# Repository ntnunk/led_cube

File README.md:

8x8x8 LED Cube
----

My 8x8x8 LED Cube project. This repository will eventually contain both code and circuit schematics.
Schematics and printed circuit boards designed in Kicad.

### Concept

The cube is composed of eight layers of eight LEDs per side, or sixty-four LEDs per layer. The cube
relies upon persistance of vision, much like a flourescent light, which means there is never
actually more than one LED layer active at a time. Because the controller cycles through the layers
so quickly it fools the human eye and appears as though the cube is lit continuously.

The LED cube itself is constructed of layers and columns of LEDs. The anodes every LED in a given
column are connected together while the cathodes of every LED in a given layer are connected
together. Individual LEDs can be turned on by having power applied to the vertical column the LED is
part of and then having the layer it's part of switched to ground.

## Functionality

#### Controller and Decoder

The controller for this project is essentially a simplified Arduino Duemilanove with an ATMEL
ATMEGA328P processor. A 74HC238 3-to-8 decoder is used to select one of eight general purpose NPN
transistors. The eight transistors have the base connected to an output pin of the decoder, the
emitter to ground, and the collector to the cathodes of the LEDs in the transistor's associated
layer. Since the cathodes of all LEDs on a given layer are connected together, turning on one of the
layer enable transistors connects the cathodes of that layer's LEDs to ground, causing any LEDs in
the layer with power applied to their anodes to turn on.

#### LED Driver

The second major section is the LED driver. Since the controller doesn't have enough GPIO pins to
control the number of LEDs required, another 74HC238 3-to-8 decoder is used in conjunction with
eight 74HC595N serial-in, parallel-out 8-bit shift registers to control the 64 LEDs on a layer. The
shift registers could be connected in serial, removing the need for the extra decoder, but that
would require 64 clock cycles per layer change to push all the LED enable bits into the 8
daisy-chained shift registers. Instead, the shift registers are connected in parallel with each
shift register IC (integrated circuit) controlling an individual LED on each row of the layer. So,
for example, the first 8-bit shift register controls the first LED in all eight of the rows on a
layer. 

#### Operation

The processor enables the three input lines on the decoder chip based on which LEDs on the first
row are indicated by the control program. The decoder sets the 8 output lines based on the 3 input
lines. The 8 output lines are sent to the serial in of each shift register, the processor toggles
the serial clock to move the shift registers one position, then the process repeats until all 8
output lines of all 8 shift registers are set as desired for the layer. 

The shift register output lines drive the anodes of all the LEDs on the layer. Once the processor
switches the cathodes of the layer to ground via the layer enable transistors as described above,
the enabled LEDs in the layer will light up and stay lit until the processor sets up and enables the
next layer in the sequence.

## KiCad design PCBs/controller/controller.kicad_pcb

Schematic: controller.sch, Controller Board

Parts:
C1, C9, C10: 0.1uF; CP_Radial_Tantal_D5.0mm_P2.50mm
C2: 1000uF; CP_Radial_D8.0mm_P3.50mm
C3, C7, C11: 10uF; CP_Radial_D5.0mm_P2.00mm
C4: 0.1uF; C_Disc_D8.0mm_W2.5mm_P5.00mm
C5, C6: 22pF; C_Disc_D4.7mm_W2.5mm_P5.00mm
C8: 0.1uF; CP_Radial_D5.0mm_P2.00mm
D1: LED; LED_D5.0mm
D2, D3: 1N4001; D_T-1_P5.08mm_Horizontal
J1: +12V_IN; PINHEAD1-2
J2: PWR_SW; PINHEAD1-2
J3: SERIAL; PINHEAD1-6
J4: PROG; IDC_Header_Straight_6pins
J5: +5V_OUT; PINHEAD1-2
J6: DRV_SIG1; IDC_Header_Straight_8pins
J7: DRV_SIG2; IDC_Header_Straight_8pins
J8: LAYER_EN; IDC_Header_Straight_8pins
Q1, Q2, Q3, Q4, Q5, Q6, Q7, Q8: 2N3700; TO-92_Molded_Narrow
R1, R4: 1K; R_Axial_DIN0207_L6.3mm_D2.5mm_P10.16mm_Horizontal
R2, R3: 10k; R_Axial_DIN0207_L6.3mm_D2.5mm_P10.16mm_Horizontal
R5, R6, R7, R8, R9, R10, R11, R12, R13: 330; R_Axial_DIN0207_L6.3mm_D2.5mm_P10.16mm_Horizontal
SW1: DBG_SW; SW_PUSH_6mm
SW2: RESET_SW; SW_PUSH_6mm
U1: ATMEGA328-PU; DIP-28_W7.62mm_Socket
U2: LM317T; TO-220
U3, U4: 74HC238; DIP-16_W7.62mm_Socket
Y1: 16MHz; Crystal_HC49-U_Vertical

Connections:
+5V: C1.1, C9.1, C10.1, R2.2, R3.2, U1.7 (VCC), U1.20 (AVCC), U3.16 (VCC), U4.16 (VCC)
/+12VDC: C2.1, C3.1, C4.1, D1.2 (A), D2.1 (K), J2.2, U2.1 (IN)
/B1_SER1: J6.1, U3.15 (Y0)
/B1_SER2: J6.2, U3.14 (Y1)
/B1_SER3: J6.3, U3.13 (Y2)
/B1_SER4: J6.4, U3.12 (Y3)
/B2_SER5: J7.1, U3.11 (Y4)
/B2_SER6: J7.2, U3.10 (Y5)
/B2_SER7: J7.3, U3.9 (Y6)
/B2_SER8: J7.4, U3.7 (Y7)
/LAYER1_EN: J8.1, Q1.3
/LAYER2_EN: J8.2, Q2.3
/LAYER3_EN: J8.3, Q3.3
/LAYER4_EN: J8.4, Q4.3
/LAYER5_EN: J8.5, Q5.3
/LAYER6_EN: J8.6, Q6.3
/LAYER7_EN: J8.7, Q7.3
/LAYER8_EN: J8.8, Q8.3
/RCLK: J6.8, J7.8, U1.24 ((PCINT9/ADC1)PC1)
/SRCLK: J6.7, J7.7, U1.23 ((PCINT8/ADC0)PC0)
unnamed: C5.1, U1.9 ((PCINT6/XTAL1/TOSC1)PB6), Y1.1
unnamed: C6.1, U1.10 ((PCINT7/XTAL2/TOSC2)PB7), Y1.2
unnamed: C7.1, D3.2 (A), R4.1, R5.2, U2.3 (ADJ)
unnamed: C8.1, C11.1, D2.2 (A), D3.1 (K), J5.1, R5.1, U2.2 (OUT)
unnamed: D1.1 (K), R1.1
unnamed: J1.2, J2.1
unnamed: J3.4, U1.2 ((PCINT16/RXD)PD0)
unnamed: J3.5, U1.3 ((PCINT17/TXD)PD1)
unnamed: J4.1, U1.18 ((PCINT4/MISO)PB4)
unnamed: J4.3, U1.19 ((PCINT5/SCK)PB5)
unnamed: J4.4, U1.17 ((PCINT3/OC2A/MOSI)PB3)
unnamed: J4.5, R3.1, SW2.2, U1.1 ((PCINT14/~RESET~)PC6)
unnamed: Q1.2, R6.1
unnamed: Q2.2, R7.1
unnamed: Q3.2, R8.1
unnamed: Q4.2, R9.1
unnamed: Q5.2, R10.1
unnamed: Q6.2, R11.1
unnamed: Q7.2, R12.1
unnamed: Q8.2, R13.1
unnamed: R2.1, SW1.2, U1.12 ((PCINT22/OC0A/AIN0)PD6)
unnamed: R6.2, U4.15 (Y0)
unnamed: R7.2, U4.14 (Y1)
unnamed: R8.2, U4.13 (Y2)
unnamed: R9.2, U4.12 (Y3)
unnamed: R10.2, U4.11 (Y4)
unnamed: R11.2, U4.10 (Y5)
unnamed: R12.2, U4.9 (Y6)
unnamed: R13.2, U4.7 (Y7)
unnamed: U1.4 ((PCINT18/INT0)PD2), U4.6 (G1)
unnamed: U1.5 ((PCINT19/OC2B/INT1)PD3), U4.1 (A)
unnamed: U1.6 ((PCINT20/XCK/T0)PD4), U4.2 (B)
unnamed: U1.11 ((PCINT21/OC0B/T1)PD5), U4.3 (C)
unnamed: U1.25 ((PCINT10/ADC2)PC2), U3.6 (G1)
unnamed: U1.26 ((PCINT11/ADC3)PC3), U3.1 (A)
unnamed: U1.27 ((PCINT12/SDA/ADC4)PC4), U3.2 (B)
unnamed: U1.28 ((PCINT13/SCL/ADC5)PC5), U3.3 (C)

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
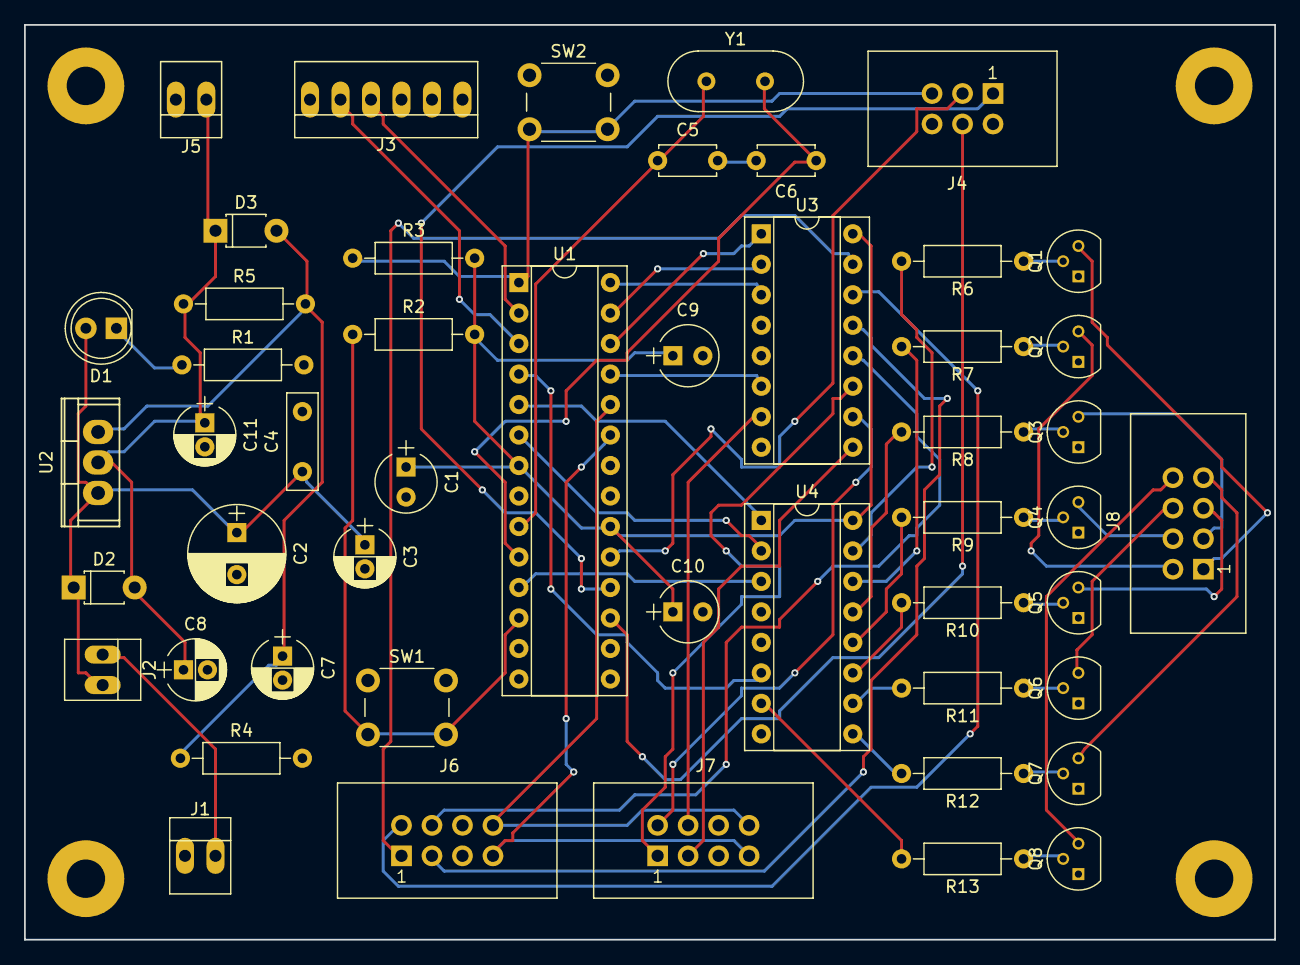
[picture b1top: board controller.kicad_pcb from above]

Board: 2 copper layers, 104.1 x 76.2 mm, 50 parts (0 on the bottom side), 59 nets.

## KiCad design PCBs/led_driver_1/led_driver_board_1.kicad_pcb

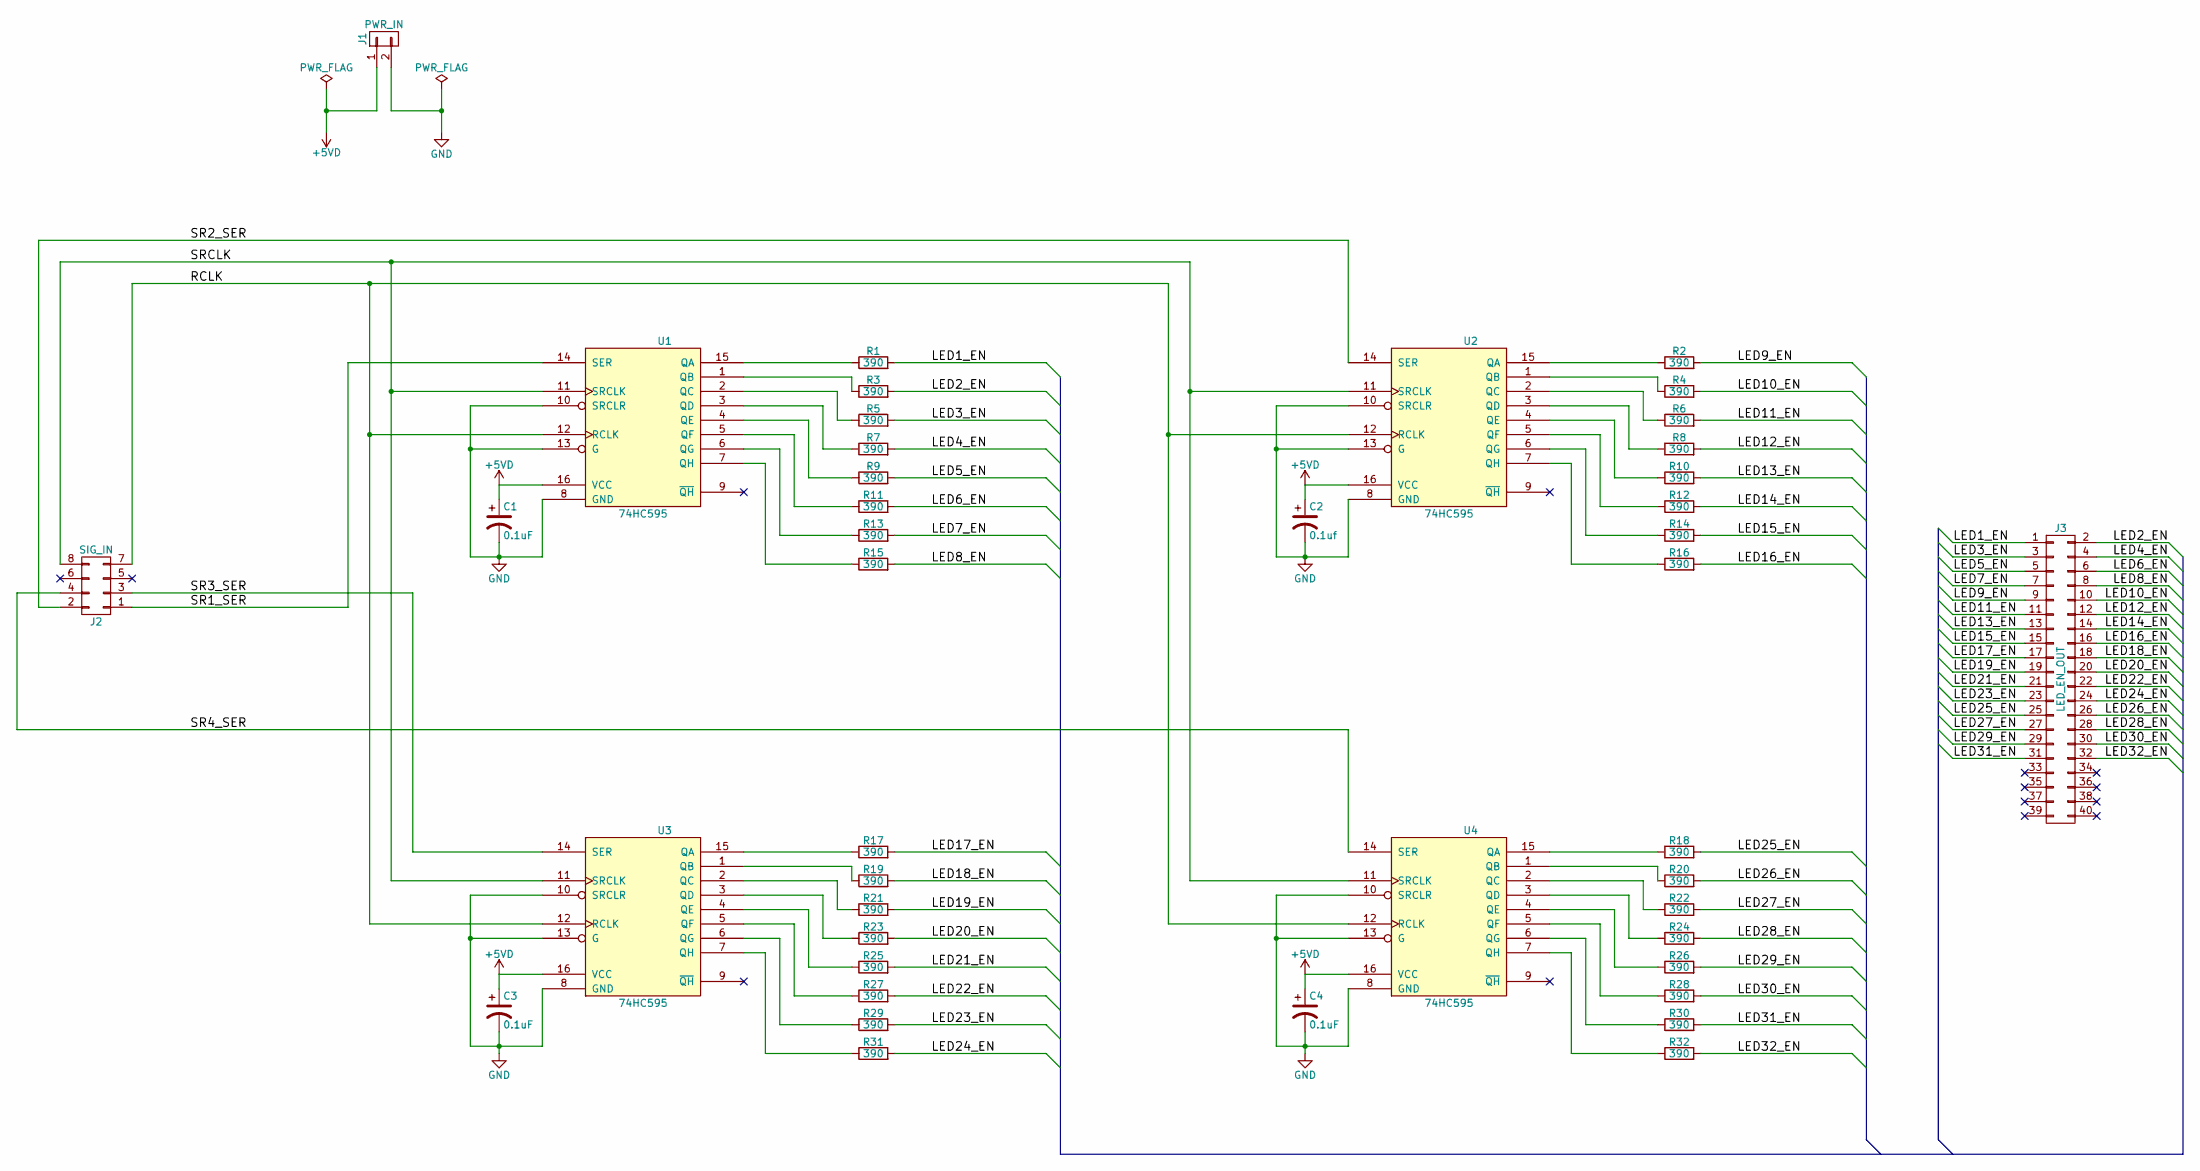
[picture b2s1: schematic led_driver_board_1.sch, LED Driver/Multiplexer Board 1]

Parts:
C1, C3, C4: 0.1uF; CP_Radial_Tantal_D5.0mm_P2.50mm
C2: 0.1uf; CP_Radial_Tantal_D5.0mm_P2.50mm
J1: PWR_IN; PINHEAD1-2
J2: SIG_IN; IDC_Header_Straight_8pins
J3: LED_EN_OUT; IDC_Header_Straight_40pins
R1, R2, R3, R4, R5, R6, R7, R8, R9, R10, R11, R12, R13, R14, R15, R16, R17, R18, R19, R20, R21, R22, R23, R24, R25, R26, R27, R28, R29, R30, R31, R32: 390; R_Axial_DIN0207_L6.3mm_D2.5mm_P10.16mm_Horizontal
U1, U2, U3, U4: 74HC595; DIP-16_W7.62mm_Socket

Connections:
+5VD: C1.1, C2.1, C3.1, C4.1, J1.1, U1.16 (VCC), U2.16 (VCC), U3.16 (VCC), U4.16 (VCC)
/LED1_EN: J3.1, R1.2
/LED2_EN: J3.2, R3.2
/LED3_EN: J3.3, R5.2
/LED4_EN: J3.4, R7.2
/LED5_EN: J3.5, R9.2
/LED6_EN: J3.6, R11.2
/LED7_EN: J3.7, R13.2
/LED8_EN: J3.8, R15.2
/LED9_EN: J3.9, R2.2
/LED10_EN: J3.10, R4.2
/LED11_EN: J3.11, R6.2
/LED12_EN: J3.12, R8.2
/LED13_EN: J3.13, R10.2
/LED14_EN: J3.14, R12.2
/LED15_EN: J3.15, R14.2
/LED16_EN: J3.16, R16.2
/LED17_EN: J3.17, R17.2
/LED18_EN: J3.18, R19.2
/LED19_EN: J3.19, R21.2
/LED20_EN: J3.20, R23.2
/LED21_EN: J3.21, R25.2
/LED22_EN: J3.22, R27.2
/LED23_EN: J3.23, R29.2
/LED24_EN: J3.24, R31.2
/LED25_EN: J3.25, R18.2
/LED26_EN: J3.26, R20.2
/LED27_EN: J3.27, R22.2
/LED28_EN: J3.28, R24.2
/LED29_EN: J3.29, R26.2
/LED30_EN: J3.30, R28.2
/LED31_EN: J3.31, R30.2
/LED32_EN: J3.32, R32.2
/RCLK: J2.7, U1.12 (RCLK), U2.12 (RCLK), U3.12 (RCLK), U4.12 (RCLK)
/SR1_SER: J2.1, U1.14 (SER)
/SR2_SER: J2.2, U2.14 (SER)
/SR3_SER: J2.3, U3.14 (SER)
/SR4_SER: J2.4, U4.14 (SER)
/SRCLK: J2.8, U1.11 (SRCLK), U2.11 (SRCLK), U3.11 (SRCLK), U4.11 (SRCLK)
GND: C1.2, C2.2, C3.2, C4.2, J1.2, U1.8 (GND), U1.10 (SRCLR), U1.13 (G), U2.8 (GND), U2.10 (SRCLR), U2.13 (G), U3.8 (GND), U3.10 (SRCLR), U3.13 (G), U4.8 (GND), U4.10 (SRCLR), U4.13 (G)
unnamed: R1.1, U1.15 (QA)
unnamed: R2.1, U2.15 (QA)
unnamed: R3.1, U1.1 (QB)
unnamed: R4.1, U2.1 (QB)
unnamed: R5.1, U1.2 (QC)
unnamed: R6.1, U2.2 (QC)
unnamed: R7.1, U1.3 (QD)
unnamed: R8.1, U2.3 (QD)
unnamed: R9.1, U1.4 (QE)
unnamed: R10.1, U2.4 (QE)
unnamed: R11.1, U1.5 (QF)
unnamed: R12.1, U2.5 (QF)
unnamed: R13.1, U1.6 (QG)
unnamed: R14.1, U2.6 (QG)
unnamed: R15.1, U1.7 (QH)
unnamed: R16.1, U2.7 (QH)
unnamed: R17.1, U3.15 (QA)
unnamed: R18.1, U4.15 (QA)
unnamed: R19.1, U3.1 (QB)
unnamed: R20.1, U4.1 (QB)
unnamed: R21.1, U3.2 (QC)
unnamed: R22.1, U4.2 (QC)
unnamed: R23.1, U3.3 (QD)
unnamed: R24.1, U4.3 (QD)
unnamed: R25.1, U3.4 (QE)
unnamed: R26.1, U4.4 (QE)
unnamed: R27.1, U3.5 (QF)
unnamed: R28.1, U4.5 (QF)
unnamed: R29.1, U3.6 (QG)
unnamed: R30.1, U4.6 (QG)
unnamed: R31.1, U3.7 (QH)
unnamed: R32.1, U4.7 (QH)

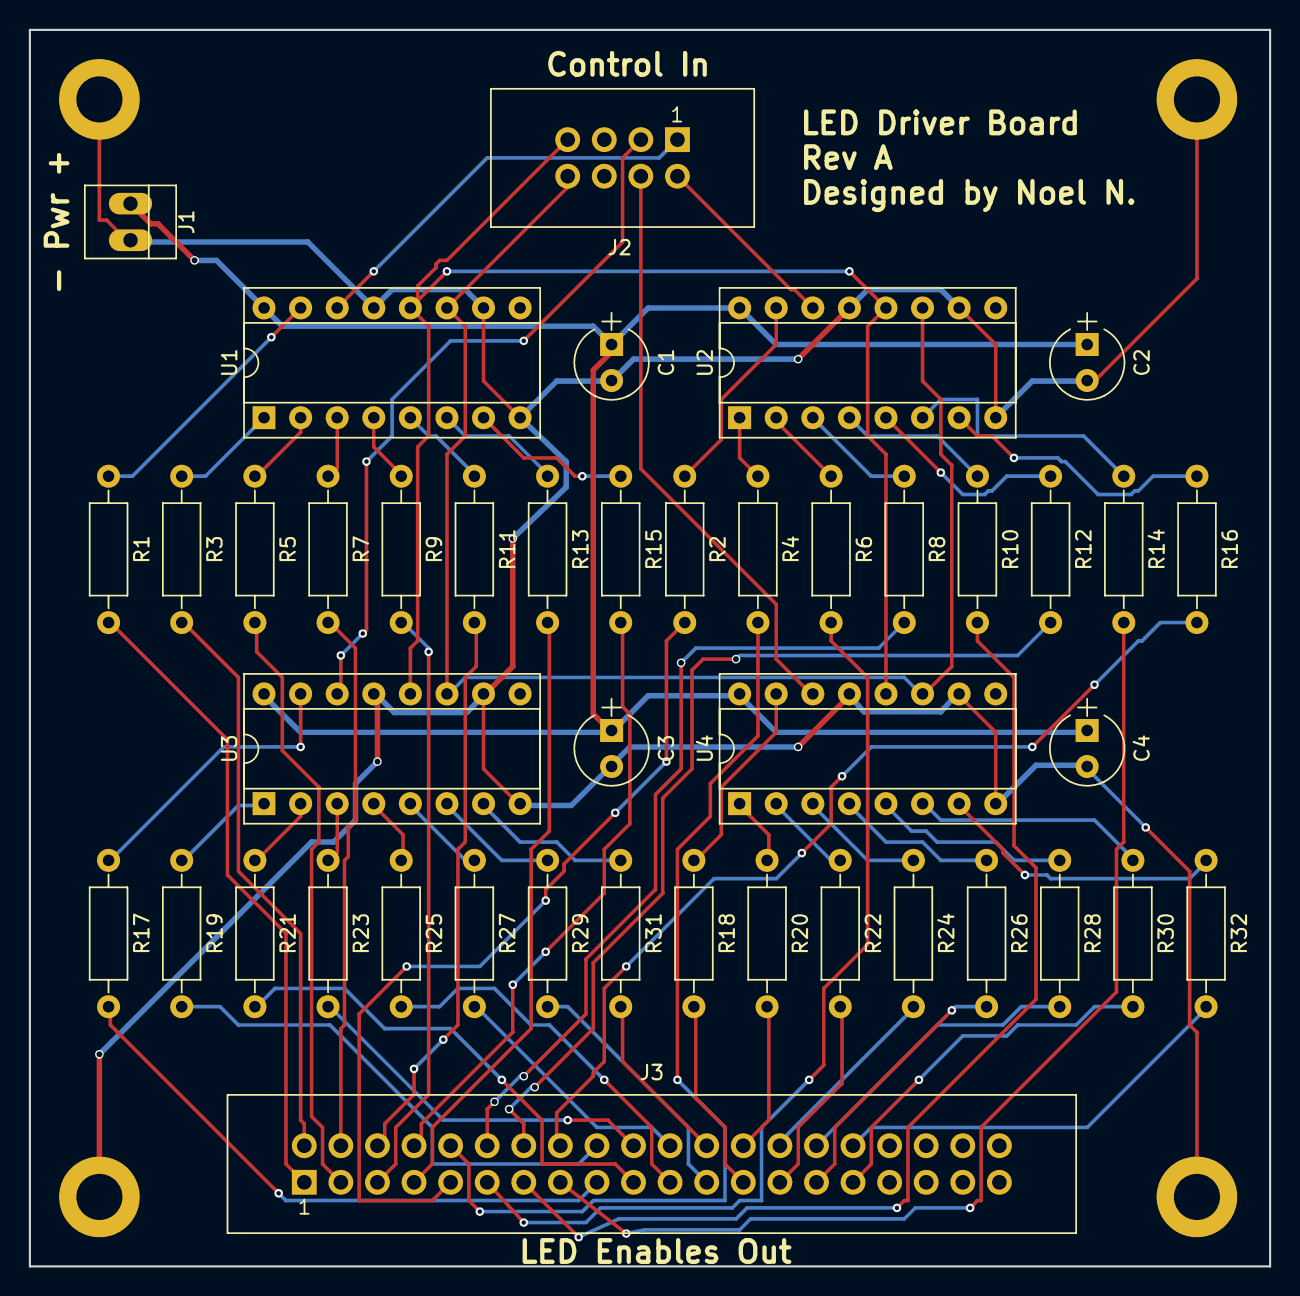
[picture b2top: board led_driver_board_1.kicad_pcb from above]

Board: 2 copper layers, 86.1 x 85.9 mm, 43 parts (0 on the bottom side), 72 nets.

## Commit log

2017-09-05 First draft
2017-09-05 Updates to README
2017-09-05 Add 2nd driver board
2017-09-05 Add LED Cube schematic
2017-09-05 Refactor to separate board projects
2017-09-06 Update project structure for multiple PCBs
2017-09-06 Driver mod and PCB layout
2017-09-06 Updates for PCB fabrication
2017-09-07 Controller footprints
2017-09-07 First controller PCB layout
2017-09-29 Corrections
2017-09-29 Updates and corrections
2017-11-14 README formatting
